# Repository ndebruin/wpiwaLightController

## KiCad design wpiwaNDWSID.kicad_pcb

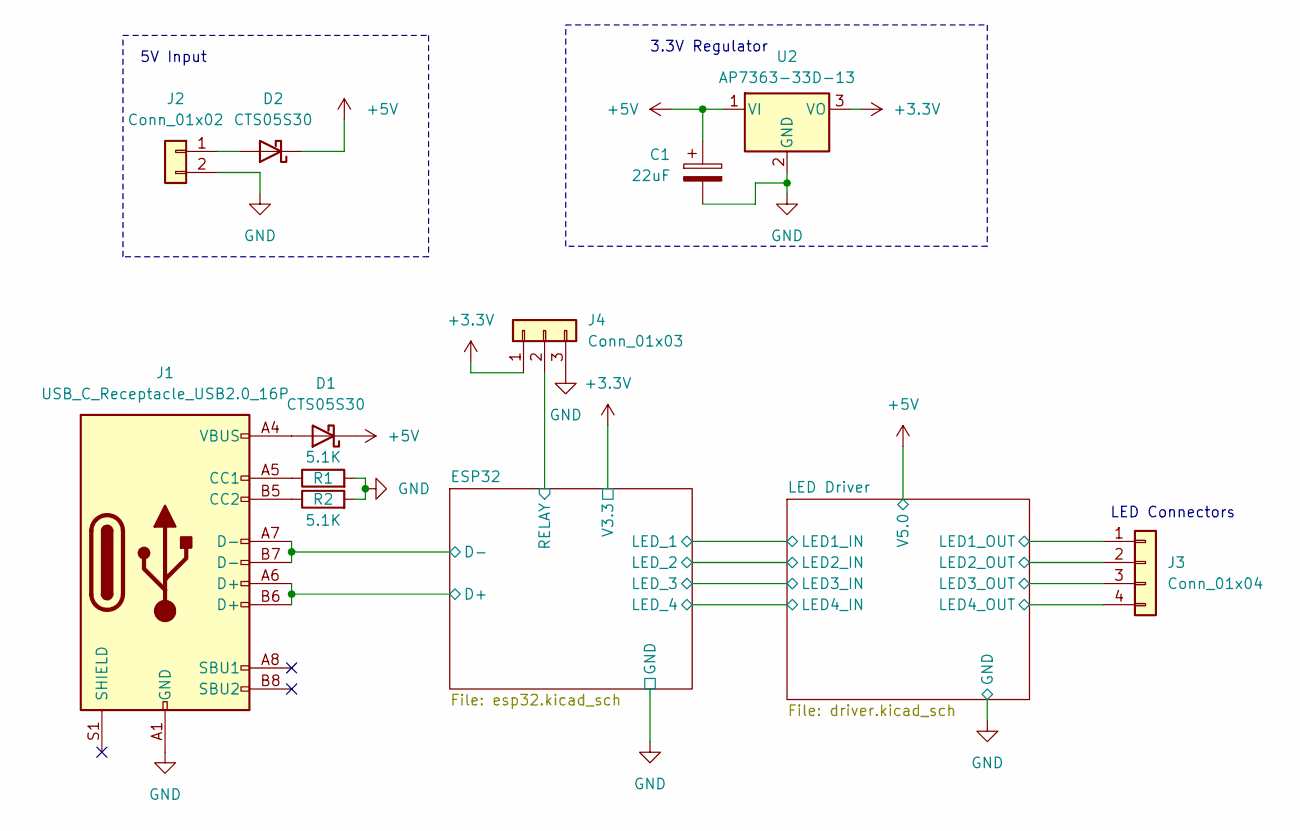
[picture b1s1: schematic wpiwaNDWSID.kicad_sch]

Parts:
C1: 22uF; CP_Radial_D4.0mm_P2.00mm
D1, D2: CTS05S30; D_0402_1005Metric_Pad0.77x0.64mm_HandSolder
J1: USB_C_Receptacle_USB2.0_16P; USB_C_Receptacle_GCT_USB4105-xx-A_16P_TopMnt_Horizontal
J2: Conn_01x02; SolderWire-0.75sqmm_1x02_P4.8mm_D1.25mm_OD2.3mm
J3: Conn_01x04; SolderWire-0.75sqmm_1x04_P4.8mm_D1.25mm_OD2.3mm
J4: Conn_01x03; SolderWire-0.75sqmm_1x03_P4.8mm_D1.25mm_OD2.3mm
R1, R2: 5.1K; R_0402_1005Metric
U2: AP7363-33D-13; TO-252-3_TabPin2

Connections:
+3.3V: J4.1, U2.3 (VO); also elsewhere on the board
+5V: C1.1, D1.1 (K), D2.1 (K), U2.1 (VI); also elsewhere on the board
/ESP32/D+: J1.A6 (D+), J1.B6 (D+); also elsewhere on the board
/ESP32/D-: J1.A7 (D-), J1.B7 (D-); also elsewhere on the board
/ESP32/RELAY: J4.2; also elsewhere on the board
/LED Driver/LED1_OUT: J3.1; also elsewhere on the board
/LED Driver/LED2_OUT: J3.2; also elsewhere on the board
/LED Driver/LED3_OUT: J3.3; also elsewhere on the board
/LED Driver/LED4_OUT: J3.4; also elsewhere on the board
GND: C1.2, J1.A1 (GND), J1.A12 (GND), J1.B1 (GND), J1.B12 (GND), J2.2, J4.3, R1.2, R2.2, U2.2 (GND); also elsewhere on the board
unnamed: D1.2 (A), J1.A4 (VBUS), J1.A9 (VBUS), J1.B4 (VBUS), J1.B9 (VBUS)
unnamed: D2.2 (A), J2.1
unnamed: J1.A5 (CC1), R1.1
unnamed: J1.B5 (CC2), R2.1

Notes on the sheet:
LED Connectors
3.3V Regulator
5V Input

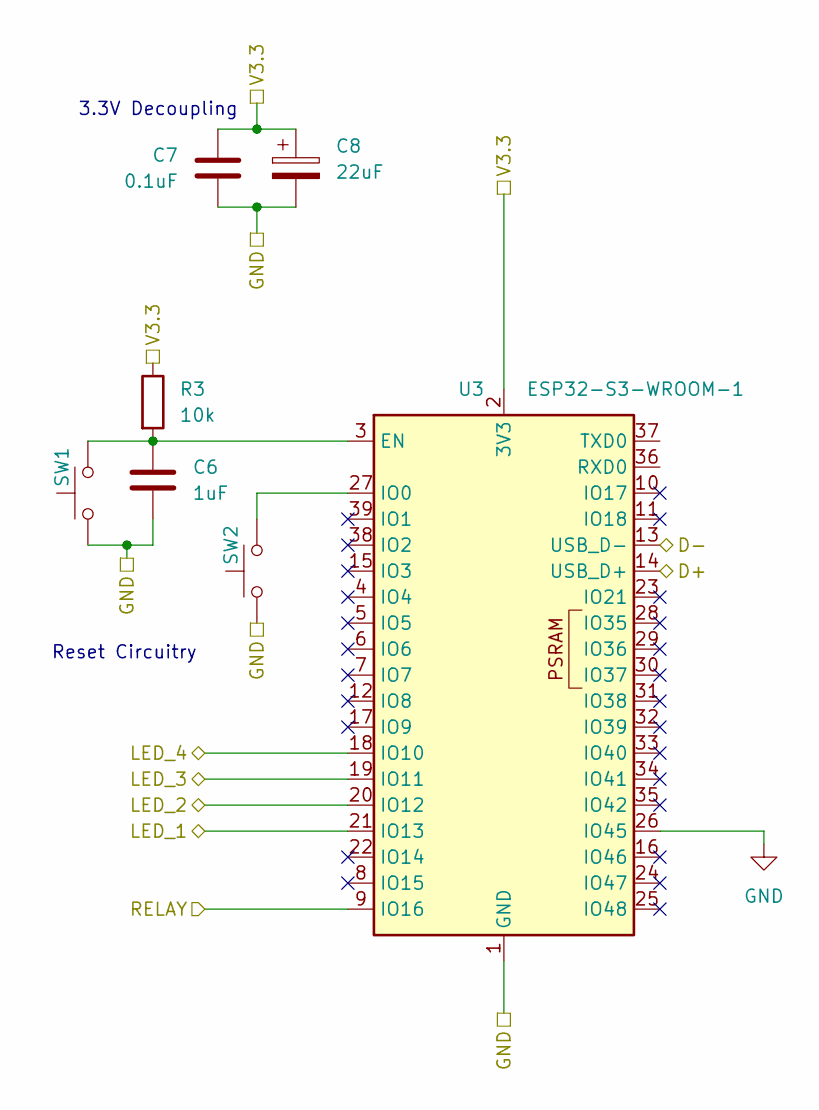
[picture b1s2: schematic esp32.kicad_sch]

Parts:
C6: 1uF; C_0402_1005Metric
C7: 0.1uF; C_0402_1005Metric
C8: 22uF; CP_Radial_D4.0mm_P2.00mm
R3: 10k; R_0402_1005
SW1, SW2: SW_Push; SW_Push_1P1T_XKB_TS-1187A
U3: ESP32-S3-WROOM-1; ESP32-S3-WROOM-1U

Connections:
+3.3V: C7.1, C8.1, R3.1, U3.2 (3V3); also elsewhere on the board
/ESP32/D+: U3.14 (USB_D+); also elsewhere on the board
/ESP32/D-: U3.13 (USB_D-); also elsewhere on the board
/ESP32/LED_1: U3.21 (IO13); also elsewhere on the board
/ESP32/LED_2: U3.20 (IO12); also elsewhere on the board
/ESP32/LED_3: U3.19 (IO11); also elsewhere on the board
/ESP32/LED_4: U3.18 (IO10); also elsewhere on the board
/ESP32/RELAY: U3.9 (IO16); also elsewhere on the board
GND: C6.2, C7.2, C8.2, SW1.1, SW2.1, U3.1 (GND), U3.26 (IO45), U3.40 (GND), U3.41 (GND); also elsewhere on the board
unnamed: C6.1, R3.2, SW1.2, U3.3 (EN)
unnamed: SW2.2, U3.27 (IO0)

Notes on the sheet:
3.3V Decoupling
Reset Circuitry

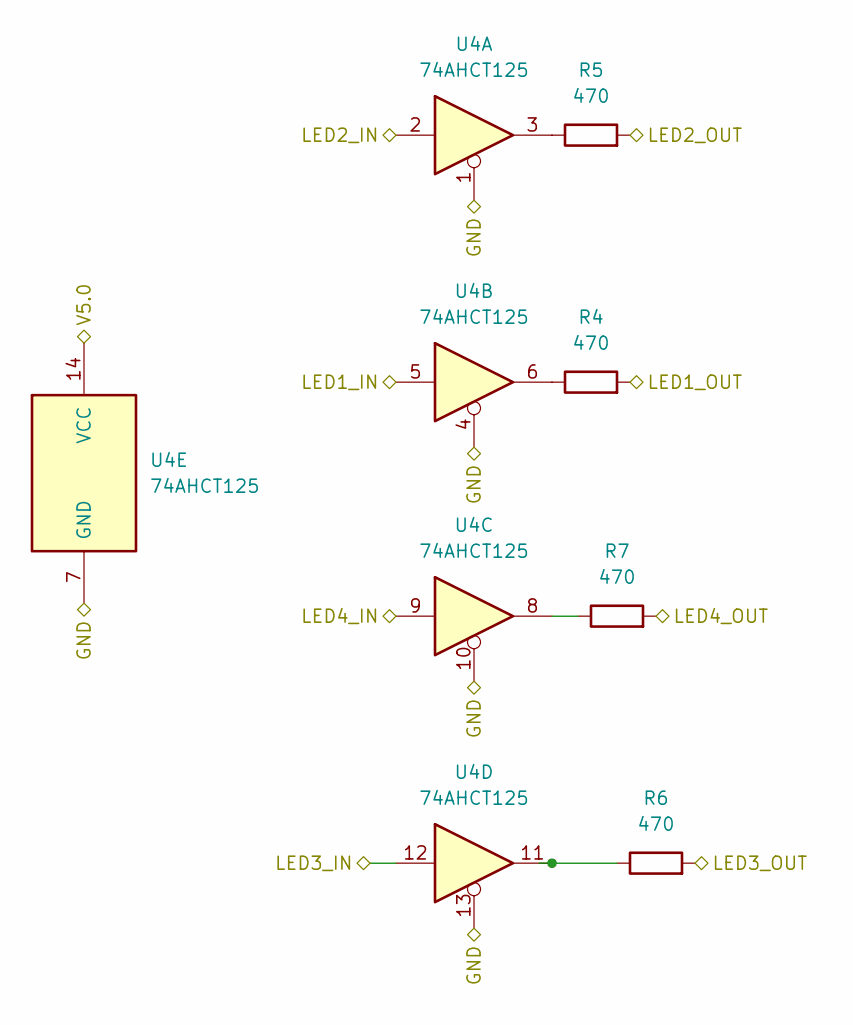
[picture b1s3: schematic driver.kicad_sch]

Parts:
R4, R5, R6, R7: 470; R_0402_1005Metric_Pad0.72x0.64mm_HandSolder
U4: 74AHCT125; SOIC-14_3.9x8.7mm_P1.27mm

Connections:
+5V: U4.14 (VCC); also elsewhere on the board
/ESP32/LED_1: U4.5; also elsewhere on the board
/ESP32/LED_2: U4.2; also elsewhere on the board
/ESP32/LED_3: U4.12; also elsewhere on the board
/ESP32/LED_4: U4.9; also elsewhere on the board
/LED Driver/LED1_OUT: R4.2; also elsewhere on the board
/LED Driver/LED2_OUT: R5.2; also elsewhere on the board
/LED Driver/LED3_OUT: R6.2; also elsewhere on the board
/LED Driver/LED4_OUT: R7.2; also elsewhere on the board
GND: U4.1, U4.4, U4.7 (GND), U4.10, U4.13; also elsewhere on the board
unnamed: R4.1, U4.6
unnamed: R5.1, U4.3
unnamed: R6.1, U4.11
unnamed: R7.1, U4.8

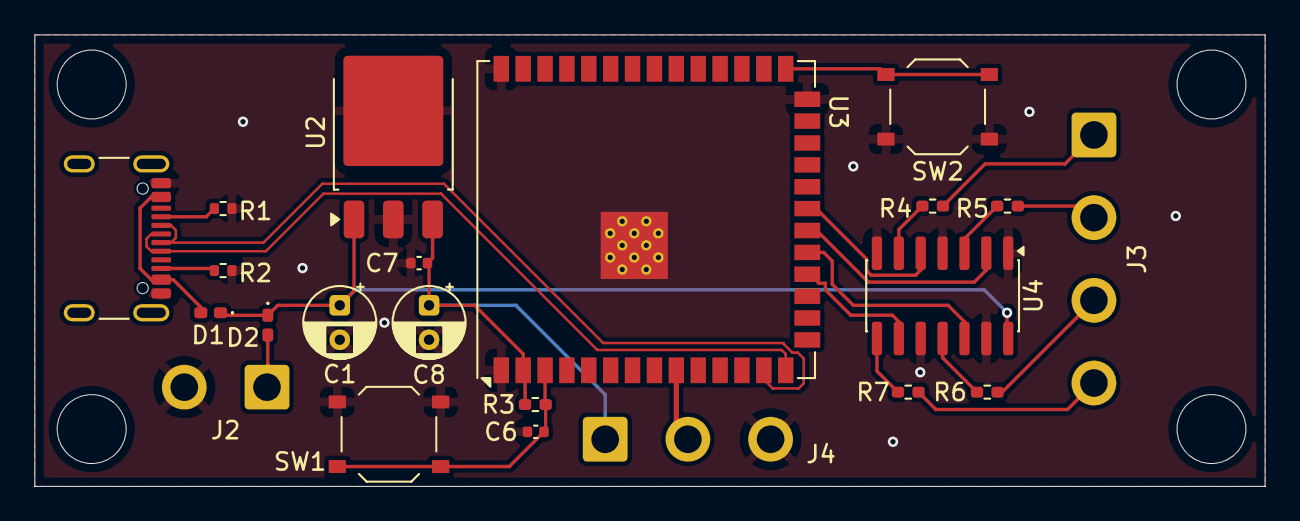
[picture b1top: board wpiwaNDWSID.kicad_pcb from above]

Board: 2 copper layers, 71.4 x 26.2 mm, 22 parts (0 on the bottom side), 24 nets.

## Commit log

2025-10-28 initial commit, pcb needs to be routed
2025-10-30 final design
2025-10-31 all one layer added usb
2025-11-02 final commit
2025-12-13 rev 2
